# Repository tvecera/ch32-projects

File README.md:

# CH32 Projects

A collection of example projects and experiments for CH32-series microcontrollers from WCH (Nanjing Qinheng
Microelectronics). This repository serves as a personal playground for embedded development with CH32 devices, focusing
on low-cost, open-source hardware hacking.

## Featured Projects

### picopad-ch32prog

- **Description**: RISC-V microcontroller programmer for WCH CH32V, CH32V00X, and CH32V03X series, running on the
  Picopad handheld device. It enables programming CH32 microcontrollers directly from the Picopad's SD card without
  requiring a PC connection.
- **Repository**: [tvecera/ch32-projects/tree/main/picopad-ch32prog](https://github.com/tvecera/ch32-projects/tree/main/picopad-ch32prog)

### ch32-lamp – Music Player (BeatleBeat)

- **Description**: Music module for playing mono WAV (IMA ADPCM) files from an SD card. Based on the BeatleBeat design
  from CH32LibSDK, using the CH32V002x4 MCU. Features BTL PWM output for louder sound without external amplifier.
- **Repository**: [tvecera/ch32-projects/tree/main/ch32-lamp](https://github.com/tvecera/ch32-projects/tree/main/ch32-lamp)

### Tinyboy Console

- **Description**: An adaptation of the CH32V003-GameConsole project by Stefan Wagner for CH32LibSDK, using the
  newer CH32V002J4M6 MCU instead of the discontinued CH32V003. Supports two video outputs: original I2C OLED display
  or RCA composite video output using the rca-library.
- **Repository**: [tvecera/ch32-projects/tree/main/tinyboy](https://github.com/tvecera/ch32-projects/tree/main/tinyboy)

### Olimex RVPC Port to CH32LibSDK

- **Description**: Port of the RVPC (the EURO 1.00 RISC-V personal computer with VGA, keyboard, and Woz-like monitor)
  from Olimex to the CH32LibSDK. In addition to the SDK port, RCA composite video output support has been added
  using the rca-library.
- **Repository**: [tvecera/ch32-projects/tree/main/rvpc](https://github.com/tvecera/ch32-projects/tree/main/rvpc)

### RCA Composite Video Library

- **Description**: A library for generating composite video signal (RCA output) on CH32V002/CH32V003 microcontrollers.
  Supports multiple graphics modes (128x64, 160x120) and text modes (40x30, 32x24, 23x18 characters) with minimal
  RAM and Flash usage. Features both bit-bang and SPI output modes, works with internal oscillator (HSI) or external
  crystal (HSE).
- **Repository**: [tvecera/ch32-projects/tree/main/rca-library](https://github.com/tvecera/ch32-projects/tree/main/rca-library)

### RCA Tester

- **Description**: A simple composite video tester and demonstration of the rca-library capabilities. Generates
  PAL composite video signals with multiple test patterns (grid, crosshatch, circles, checkerboard, etc.) and text
  modes with various fonts. Includes complete hardware design files for DIY manufacturing (KiCAD schematics, PCB
  for laser etching, 3D printable case). Supports both CH32LibSDK and ch32fun frameworks.
- **Repository**: [tvecera/ch32-projects/tree/main/rca-tester](https://github.com/tvecera/ch32-projects/tree/main/rca-tester)

### Pimitachi – 3D Case and Labels

- **Description**: 3D printable case, labels, and laser-etched PCB design for Pimitachi – a Tamagotchi-style virtual pet
  game running on the CH32V002J4M6 MCU. Includes LightBurn project for PCB fabrication with a 10W laser engraver,
  printable labels (photo paper + transparent film), and assembly instructions.
- **Original project**: [Pimitachi on breatharian.eu](https://www.breatharian.eu/hw/ch32libsdk/#pimitachi)
- **Repository**: [tvecera/ch32-projects/tree/main/pimitachi](https://github.com/tvecera/ch32-projects/tree/main/pimitachi)

## Supported Platforms

Build system supports **Linux** and **macOS** (both x86_64 and ARM64/Apple Silicon).

## Getting Started

### Cloning the Repository

This repository uses Git submodules for SDK dependencies. Clone with:

```bash
git clone --recursive https://github.com/tvecera/ch32-projects.git
```

Or if you already cloned without `--recursive`:

```bash
git submodule update --init --recursive
```

### SDK Submodules

The repository includes three SDK submodules in the `sdk/` directory:

| SDK | Description |
|-----|-------------|
| [CH32LibSDK](https://github.com/Panda381/CH32LibSDK) | SDK for CH32V/X series MCUs |
| [PicoLibSDK](https://github.com/Panda381/PicoLibSDK) | SDK for Raspberry Pi Pico / RP2040 / RP2350 |
| [ch32fun](https://github.com/cnlohr/ch32fun) | Lightweight SDK for CH32V003 |

### Required Toolchains

Different projects require different toolchains:

#### For CH32 Projects (ch32-lamp, rvpc, rca-library, tinyboy)

- **RISC-V GCC Toolchain** - `riscv-none-elf-gcc`

**Recommended: xPack RISC-V GCC (cross-platform):**

Download pre-built binaries from [xPack RISC-V GCC releases](https://github.com/xpack-dev-tools/riscv-none-elf-gcc-xpack/releases) and add to PATH.

**macOS/Linux (npm):**
```bash
npm install --location=global @xpack-dev-tools/riscv-none-elf-gcc@latest
```

#### For Picopad Projects (picopad-ch32prog)

- **ARM GCC Toolchain** - `arm-none-eabi-gcc`

**macOS (Homebrew):**
```bash
brew install arm-none-eabi-gcc
```

**Linux (Ubuntu/Debian):**
```bash
sudo apt install gcc-arm-none-eabi
```

#### Additional Tools

- **make** - Build automation
- **minichlink** - CH32 programmer/debugger (included in `tools/minichlink/`)

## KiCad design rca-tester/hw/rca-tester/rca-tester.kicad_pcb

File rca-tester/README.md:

# RCA Tester

A while ago, I purchased a replica of the Sony Walkman CRT screen, which can be found on Chinese
e-shops for a few hundred CZK. The problem is that these screens only support composite video input.
I didn't have any device at home capable of generating a composite video signal. That's why I decided
to create a simple and inexpensive RCA tester.

The RCA Tester serves as both a practical tool for testing composite video displays and a demonstration
of the `rca-library` capabilities. It generates standard PAL composite video signals using just
a cheap RISC-V microcontroller and a few passive components.

**Version 1**

## Features

- **Composite video output** via SPI (hardware) or bit-banging (software)
- **Multiple video modes**: Graphics (pixel-based) and Text (character-based)
- **Test patterns**: 6 pre-built patterns + 2 dynamic patterns
- **Multiple fonts**: Bold, Thin, ZX Spectrum, RVPC, 80-column styles
- **Button input**: 3 buttons with debouncing and auto-repeat
- **Sound synthesis**: PWM audio with melody playback
- **Dual framework support**: Works with both CH32LibSDK and ch32fun

## Supported Microcontrollers

| MCU      | Flash | SRAM | Notes          |
|----------|-------|------|----------------|
| CH32V002 | 16 KB | 4 KB | Default target |
| CH32V003 | 16 KB | 2 KB | Alternative    |

## Video Modes

### Graphics Modes (Pixel-based framebuffer)

| Mode    | Resolution | RAM Usage | Description                 |
|---------|------------|-----------|-----------------------------|
| VMODE 0 | 128x64 px  | ~1.3 KB   | Low resolution, minimal RAM |
| VMODE 1 | 160x120 px | ~2.7 KB   | Higher resolution           |

> **Note:** VMODE 1 requires ~2.7 KB RAM and is only available on CH32V002 (4 KB SRAM).
> CH32V003 with 2 KB SRAM does not have enough memory for this mode.

### Text Modes (Character-based with fonts)

| Mode    | Dimensions  | Font Size | RAM Usage | Description       |
|---------|-------------|-----------|-----------|-------------------|
| VMODE 6 | 40x30 chars | 8x8       | ~1.6 KB   | High density text |
| VMODE 7 | 32x24 chars | 8x8       | ~1.2 KB   | Standard text     |
| VMODE 8 | 23x18 chars | 8x14      | ~0.9 KB   | Large font text   |

## Hardware

**Version 2** (+ PC7 for LED)

### Pin Configuration

| Pin         | Function        | Description                       |
|-------------|-----------------|-----------------------------------|
| **PC6**     | Video Out (SPI) | SPI1_MOSI - hardware video output |
| **PD6**     | Video Out (Alt) | Bit-banging alternative           |
| **PC1**     | Button LEFT/C   | Active-low, internal pull-up      |
| **PC2**     | Button UP/B     | Active-low, internal pull-up      |
| **PC3**     | Button RIGHT/A  | Active-low, internal pull-up      |
| **PC4**     | Audio Out       | PWM on TIM1_CH4                   |
| **PC7**     | LED             | Optional status LED               |
| **PA1/PA2** | Crystal         | External 25 MHz oscillator        |

### Clock Configuration

- **External crystal**: 25 MHz
- **PLL multiplier**: x2
- **System clock**: 50 MHz

### Hardware Design Files

The project is designed for home manufacturing. The `hw/` directory includes everything needed to build the complete
device: a PCB design for a 10W laser, a 3D printable case, and label templates. No professional PCB manufacturing or
specialized equipment (beyond a basic laser engraver and 3D printer) is required.

The `hw/` directory contains all hardware design files:

```
hw/
├── rca-tester/                  # KiCAD 9 project (schematic + PCB) - Version 2
├── rca-tester-case.3mf          # 3D printed case model
├── rca-tester-pcb.lbrn2         # LightBurn project for laser PCB etching - Version 1
├── rca-tester-pcb.png           # PCB image for manual manufacturing - Version 1
├── rca-tester-label.afdesign    # Label template (Affinity Designer)
├── rca-tester-label.docx        # Label template (Word)
└── rca-tester-digram.png        # Block diagram
```

> **Note:** The KiCAD project reflects **Version 2** of the PCB design, which includes these improvements:
> - PC7 pin exposed for optional LED connection
> - Larger crystal socket
>
> The LightBurn/PNG files contain **Version 1** (original design without these features).

#### Manual PCB Manufacturing

The `rca-tester-pcb.lbrn2` and `rca-tester-pcb.png` files are designed for DIY PCB manufacturing using a laser
engraver (10W diode laser recommended).

**Version 1**

### Bill of Materials (BOM)

| Ref     | Component       | Value/Part   | Qty | Notes                                                                                 |
|---------|-----------------|--------------|-----|---------------------------------------------------------------------------------------|
| IC1     | Microcontroller | CH32V002A4M6 | 1   | [AliExpress](https://www.aliexpress.com/item/1005008493381343.html)                   |
| Q1      | Crystal         | 25 MHz       | 1   | HC-49U/S package                                                                      |
| C1      | Capacitor       | 100 nF       | 1   | Ceramic, 1206                                                                         |
| C2, C3  | Capacitor       | 22 pF        | 2   | Ceramic, 1206                                                                         |
| R1      | Resistor        | 470 Ω        | 1   | 1206                                                                                  |
| R2      | Resistor        | 330 Ω        | 1   | 1206                                                                                  |
| R3, R4  | Resistor        | 680 Ω        | 2   | 1206                                                                                  |
| SW1-SW3 | Push Button     | 6x6 mm       | 3   | Tactile switch                                                                        |
| J1      | Header          | 1x4 pin      | 1   | Pin header                                                                            |
| J2      | RCA Connector   | RS-162-DD    | 1   | [GME](https://www.gme.cz/v/1499520/rs-162-zluta-rca-zasuvka)                          |
| J3      | Header          | 1x3 pin      | 1   | Pin header                                                                            |
| J4      | USB Connector   | Micro-B      | 1   | [AliExpress](https://www.aliexpress.com/item/1005007360060905.html) (Micro-28)        |
| BZ1     | Buzzer          | 12 mm        | 1   | [GME](https://www.gme.cz/v/1498245/al-goodwell-al12085mt-p15r-magnetodynamicky-menic) |

Most components are commonly available. The less standard parts with purchase links:

- **RCA Connector (RS-162-DD)** - Available at [GME.cz](https://www.gme.cz/v/1499520/rs-162-zluta-rca-zasuvka)
- **CH32V002A4M6** - RISC-V MCU from WCH, available
  on [AliExpress](https://www.aliexpress.com/item/1005008493381343.html)
- **Micro USB (Micro-28)** - SMD connector, available
  on [AliExpress](https://www.aliexpress.com/item/1005007360060905.html)
- **Buzzer (12 mm)** - Magnetic transducer, available
  at [GME.cz](https://www.gme.cz/v/1498245/al-goodwell-al12085mt-p15r-magnetodynamicky-menic)

## Build System

### Prerequisites

1. **Toolchain**: xpack-riscv-none-elf-gcc (recommended)
    - Download from: https://github.com/xpack-dev-tools/riscv-none-elf-gcc-xpack
    - Note: WCH toolchain has `-flto` bugs, avoid it

2. **Framework** (one of):
    - **CH32LibSDK**: https://github.com/Panda381/CH32LibSDK
    - **ch32fun**: https://github.com/cnlohr/ch32fun

3. **Environment setup**:
   ```bash
   export PATH="/path/to/xpack-riscv-none-elf-gcc/bin:$PATH"
   export CH32_ROOT_PATH="/path/to/CH32LibSDK"
   ```

### Build Scripts

All scripts accept optional parameters: `[sdk] [mcu]`

| Script | Function              | Example                      |
|--------|-----------------------|------------------------------|
| `c.sh` | Build/Compile         | `./c.sh ch32libsdk ch32v003` |
| `d.sh` | Clean                 | `./d.sh`                     |
| `e.sh` | Flash to device       | `./e.sh ch32fun ch32v002`    |
| `r.sh` | Reset device          | `./r.sh`                     |
| `a.sh` | Clean + Build         | `./a.sh`                     |
| `x.sh` | Clean + Build + Flash | `./x.sh`                     |

**Default values**: `sdk=ch32libsdk`, `mcu=ch32v002`

### Quick Start

```bash
# Full rebuild and flash with defaults
./x.sh

# Build for CH32V003 with CH32LibSDK
./x.sh ch32libsdk ch32v003

# Just compile (no flash)
./c.sh

# Clean build artifacts
./d.sh
```

## Configuration

Edit `config.h` to customize the firmware:

### Video Mode Selection

```c
#define VMODE 0     // 0=128x64, 1=160x120, 6=40x30 text, 7=32x24 text, 8=23x18 text
```

### Video Output Method

```c
#define USE_RCA_SPI 1   // 1=SPI hardware (PC6), 0=bit-bang (PD6)
```

### Clock Source

```c
#define USE_HSI 0       // 0=external 25MHz crystal, 1=internal oscillator
```

### Feature Enables

```c
#define USE_KEYS  1     // Enable button input
#define USE_SOUND 2     // 0=disabled, 1=tones only, 2=melody playback
```

## Usage

### Graphics Mode (VMODE 0/1)

The application cycles through 8 test patterns:

1. **Grid** - Regular grid lines
2. **Crosshatch** - Diagonal crossing lines
3. **Circles** - Concentric circles
4. **Border** - Screen border frame
5. **Checkerboard** - Alternating squares
6. **Dots** - Dot matrix pattern
7. **Text** - "RCA Video" text display
8. **Charset** - Full character set display

**Controls**:

- **RIGHT (A)** - Next pattern
- **LEFT (C)** - Previous pattern
- **UP (B)** - Reset to bootloader

### Text Mode (VMODE 6/7/8)

The application showcases different fonts:

- TextModeFontBold8x8
- TextModeFontThin8x8
- TextModeFontZx
- TextModeFontRvpc
- TextModeFont80
- TextModeFont81

## Pattern Conversion

The conversion scripts generate C header files containing the pattern data, which are then included in the project.

### Convert PNG to C array

```bash
cd patterns

# For VMODE 0 (128x64)
python3 convert.py vmode0/01_pattern_grid.png > pattern_grid.h

# For VMODE 1 with RLE compression (160x120)
python3 convert_rle.py vmode1/01_pattern_grid.png > pattern_grid_rle.h
```

### Requirements

- Python 3
- Pillow library: `pip3 install pillow`

## Dependencies

### rca-library

The shared video generation library located at `../rca-library/`:

- Video signal timing and generation
- Multiple font files (8x8, 8x14, various styles)
- SPI and bit-bang rendering modes
- Frame callback mechanism

### Frameworks

Both frameworks are included in the repository as git submodules in `../sdk/`:

```bash
# Initialize submodules after cloning
git submodule update --init --recursive
```

**CH32LibSDK** by Miroslav Nemecek (Panda38):

- https://github.com/Panda381/CH32LibSDK
- Location: `../sdk/CH32LibSDK/`
- Full peripheral drivers
- Comprehensive hardware abstraction

**ch32fun** by CNLohr:

- https://github.com/cnlohr/ch32fun
- Location: `../sdk/ch32fun/`
- Lightweight alternative
- Minimal overhead

## License

MIT License - See source file headers for details.

Portions derived from CH32LibSDK by Miroslav Nemecek (Panda38) retain their original license.

## Links

- [CH32LibSDK](https://github.com/Panda381/CH32LibSDK)
- [ch32fun](https://github.com/cnlohr/ch32fun)
- [RISC-V Toolchain](https://github.com/xpack-dev-tools/riscv-none-elf-gcc-xpack)

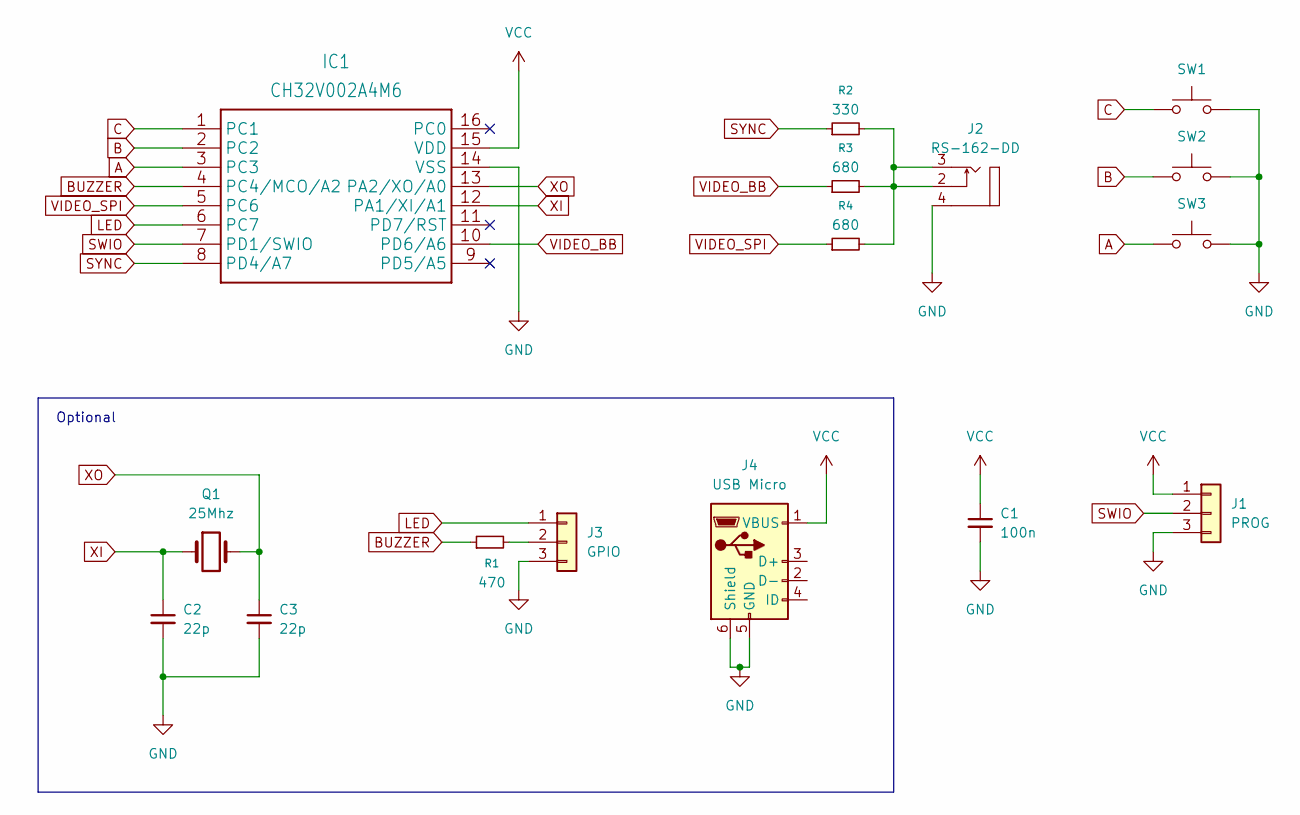
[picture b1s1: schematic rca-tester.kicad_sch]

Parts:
C1: 100n; C_1206_3216Metric_Pad1.33x1.80mm_HandSolder
C2, C3: 22p; C_1206_3216Metric_Pad1.33x1.80mm_HandSolder
IC1: CH32V002A4M6; SOP-16_4.55x10.3mm_P1.27mm
J1: PROG; PinSocket_1x03_P2.54mm_Vertical
J2: RS-162-DD
J3: GPIO; PinSocket_1x05_P2.54mm_Vertical
J4: USB Micro; USB_Micro-B_Amphenol_10118194_Horizontal
Q1: 25Mhz; PinSocket_1x03_P2.54mm_Vertical
R1: 470; R_1206_3216Metric_Pad1.30x1.75mm_HandSolder
R2: 330; R_1206_3216Metric_Pad1.30x1.75mm_HandSolder
R3, R4: 680; R_1206_3216Metric_Pad1.30x1.75mm_HandSolder
SW1, SW2, SW3: SW_Push; SW_PUSH_6mm

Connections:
A: IC1.3 (PC3), SW3.1
B: IC1.2 (PC2), SW2.1
BUZZER: IC1.4 (PC4/MCO/A2), R1.1
C: IC1.1 (PC1), SW1.1
GND: C1.2, C2.2, C3.2, IC1.14 (VSS), J1.3, J2.4, J3.3, J4.5 (GND), J4.6 (Shield), SW1.2, SW2.2, SW3.2
LED: IC1.6 (PC7), J3.1
unnamed: J2.2, J2.3, R2.2, R3.2, R4.2
unnamed: J3.2, R1.2
SWIO: IC1.7 (PD1/SWIO), J1.2
SYNC: IC1.8 (PD4/A7), R2.1
VCC: C1.1, IC1.15 (VDD), J1.1, J4.1 (VBUS)
VIDEO_BB: IC1.10 (PD6/A6), R3.1
VIDEO_SPI: IC1.5 (PC6), R4.1
XI: C2.1, IC1.12 (PA1/XI/A1), Q1.1
XO: C3.1, IC1.13 (PA2/XO/A0), Q1.2

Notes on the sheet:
Optional

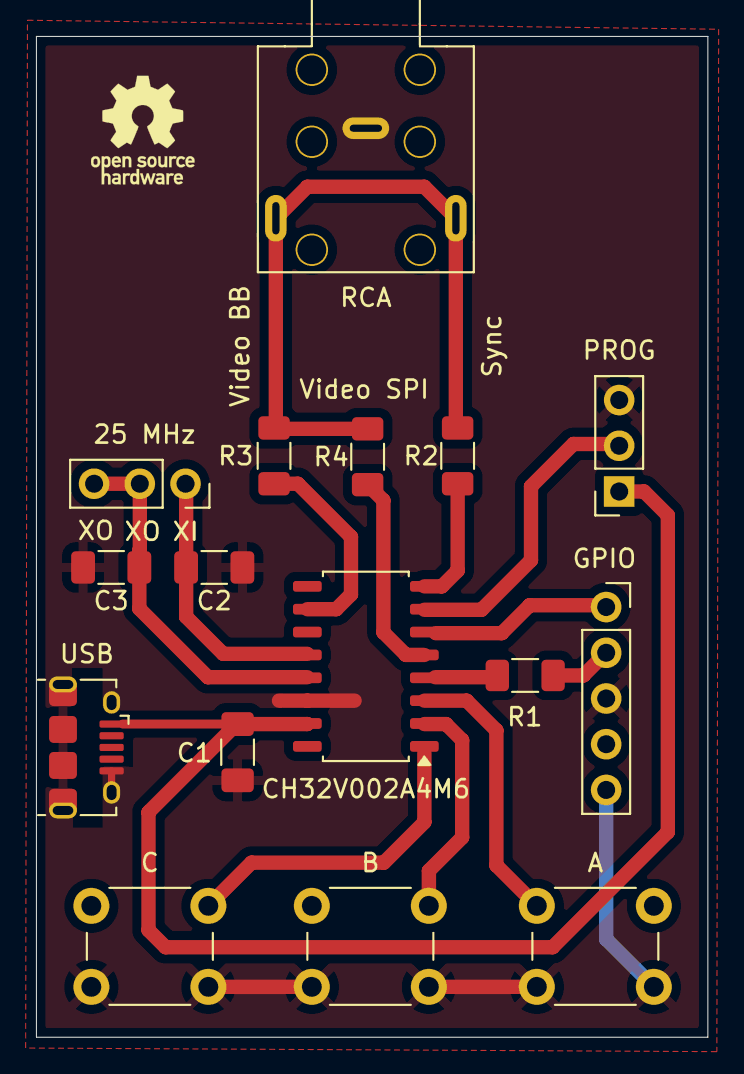
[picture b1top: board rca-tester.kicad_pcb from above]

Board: 2 copper layers, 37.3 x 55.6 mm, 16 parts (0 on the bottom side), 15 nets.

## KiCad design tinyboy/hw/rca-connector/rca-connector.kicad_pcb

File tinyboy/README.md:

bu# Tinyboy

**Tinyboy console** is based on the [CH32V003-GameConsole](https://github.com/wagiminator/CH32V003-GameConsole) project
by Stefan Wagner.  
Instead of the now discontinued CH32V003, it uses the newer **CH32V002J4M6** MCU.  
I used version 1.1 of the PCB design, which does not include the transistor for the buzzer.

**CH32V003-GameConsole PCB v1.1**

- https://oshwlab.com/wagiminator/ch32v003j4m6-game-console
- https://github.com/wagiminator/CH32V003-GameConsole/tree/main/hardware

---

## Schematic

The Tinyboy console does **not include the 6th button (KEY_B)**. Fortunately, most games in **CH32LibSDK** do not
require this button.

---

## Video Output

TinyBoy supports two video output options:

### OLED Display (I2C)

The default video output uses a **0.96" I2C OLED display** (128×64 pixels, SSD1306 controller).
This is the standard configuration inherited from the original CH32V003-GameConsole design.

### RCA Composite Video

As an alternative, you can output video to a **TV or monitor** via composite video (RCA connector).
This mode uses the [rca-library](../rca-library/) from this repository.

The I2C pins are repurposed with a simple resistor DAC:

| Pin | Resistor | Signal |
|-----|----------|--------|
| SDA | 330Ω     | SYNC   |
| SCL | 680Ω     | VIDEO  |
| GND | —        | GND    |

Connect SYNC + VIDEO to the **center pin** of the RCA connector, and GND to the **outer ring**.

#### RCA Connector Adapter

A simple adapter PCB is available in [hw/rca-connector](hw/rca-connector/) (KiCad project).

**Schematic:**

**PCB for manual fabrication:**

**Additional files:**

- [rca-connector-label.pdf](hw/rca-connector-label.pdf) – printable labels
- [rca-connector.lbrn2](hw/rca-connector.lbrn2) – LightBurn project file (for 10W laser engraver)

#### Build Configuration

Each game directory contains shell scripts for building and flashing:

| Script | Description                        |
|--------|------------------------------------|
| `c.sh` | Compile (incremental build)        |
| `a.sh` | All – clean + compile              |
| `d.sh` | Delete – clean build artifacts     |
| `e.sh` | Export – flash to hardware + reset |
| `r.sh` | Reset device                       |
| `x.sh` | Full rebuild + flash (a.sh + e.sh) |

The video output is selected by passing `0` (OLED) or `1` (RCA) as argument:

```bash
# Build for OLED display (default)
./c.sh 0

# Build for RCA composite video output
./c.sh 1

# Full clean rebuild + flash for RCA
./x.sh 1
```

For RCA mode, you can also select the video resolution using `VMODE` environment variable:

| VMODE | Resolution | Framebuffer |
|-------|------------|-------------|
| 0     | 128×64     | 1024 B      |
| 1     | 160×120    | 2400 B      |

```bash
# Build for RCA with higher resolution
VMODE=1 ./c.sh 1
```

**Note:** RCA mode uses a different clock configuration (50 MHz via PLL instead of 24 MHz HSI) to achieve accurate video
timing.

---

## Programming

Programming the console is straightforward using the **WCH-LinkE programmer**.  
Simply connect:

- **SWDIO** from programmer → **DIO**
- **3V3**
- **GND**

The standard tool is **WCH-LinkUtility**, but it is **only available for Windows**.  
For Linux and macOS, alternatives are needed:

### [rvprog](https://github.com/wagiminator/MCU-Flash-Tools?tab=readme-ov-file#rvprog)

- Easy installation (`pip install rvprog`)
- Limitation: fails to upload larger programs (>10 KB) completely into MCU flash

### [minichlink](https://github.com/cnlohr/ch32fun/tree/master/minichlink)

- The **most reliable tool** in my experience
- Can reset the MCU even without the reset pin connected
- Automatically detects the WCH-LinkE programmer
- Supports alternative programmers (e.g., via **esp32s2chfun**)
- Drawback: must be compiled manually
    - On macOS I had to remove support for `b003boot` and `esp32s2chfun` to build successfully

Prebuilt binaries for **macOS** and **Linux** are available in the `../tools` folder.

---

## Battery Measurement

A nice advantage of the Tinyboy console is that it has **no voltage regulator** – the MCU is powered directly from the
battery. This allows you to **measure the battery voltage** using the internal **1.2 V reference** of the CH32V002.

### Example Usage

```c
// The value bat will return the battery voltage in millivolts (mV).

BatInit();
const u32 bat = GetBat();
BatTerm();
```

**Notes**

- The function uses ADC1 in single conversion mode.
- The computation scales the internal 1.2 V reference to the actual supply voltage.
- If you use the KEY service, it must be temporarily disabled while reading the ADC.
- Returns the voltage in millivolts (mV).

---

## Expansion Possibilities

Because the MCU is in an **SOP-8 package**, the number of available pins is very limited.  
Still, some expansions are possible:

- The **OLED pins** can also be used to connect an **I2C sensor**.  
  With software I2C, you can easily turn the console into a **simple sensor device**.

- Another option is to reuse the **SWIO programming pin**.  
  The SDK provides functions to remap it:

```c
// PD1 as standard GPIO
GPIO_Remap_SWD(4);

// Restore PD1 as SWIO (programming)
GPIO_Remap_SWD(0);
```

⚠️ **Warning:** After remapping PD1 to GPIO, programming will no longer work.  
The only recovery option is a **power cycle erase** ("unbrick chip").  
It is therefore wise to add a small delay at the start of `main()` to allow erasing via programmer,  
or only remap this pin after pressing a button.

---

## Assembly

Assembly is relatively simple, but some parts (battery holder, on/off switch, buzzer) may be harder to source.  
**Tip:** Solder the OLED display **last** – otherwise it becomes tricky to mount the on/off switch properly.

With PCB ordered from JLCPCB, the total cost is around **100–200 CZK** (≈ 4–8 EUR).

---

## Parts List

| Component                        | Link                                                                                                                                                                                                                                                 | Price    |
|----------------------------------|------------------------------------------------------------------------------------------------------------------------------------------------------------------------------------------------------------------------------------------------------|----------|
| **MCU CH32V002J4M6**             | [AliExpress](https://www.aliexpress.com/item/1005009035485168.html)                                                                                                                                                                                  | ~2 Kč    |
| **Buzzer – MLT-5030**            | [AliExpress](https://www.aliexpress.com/item/1005008979086407.html)                                                                                                                                                                                  | ~8 Kč    |
| **Battery Holder (CR2032)**      | [AliExpress](https://www.aliexpress.com/item/1005005960185390.html), [TME](https://www.tme.eu/cz/details/ch28-2032/baterie-pouzdra-i-drzaky/comf/ch28-2032lf/)                                                                                       | 6–25 Kč  |
| **Rechargeable Battery LIR2032** | [Laskakit](https://www.laskakit.cz/lir2032-li-ion-baterie-40mah-3-6v/), [AliExpress](https://www.aliexpress.com/item/1005008971074671.html)                                                                                                          | 16–58 Kč |
| **I2C OLED 0.96" (128x64)**      | [Pajenicko](https://pajenicko.cz/graficky-oled-displej-096-128x64-i2c-bily), [AliExpress](https://www.aliexpress.com/item/1005006141235306.html)                                                                                                     | 40–89 Kč |
| **ON/OFF Switch**                | [Laskakit](https://www.laskakit.cz/alps-ssss811101-posuvny-prepinac-5vdc-300ma--smd/), [TME](https://www.tme.eu/cz/details/cus-12tb/posuvne-prepinace/nidec-copal-electronics/), [AliExpress](https://www.aliexpress.com/item/1005006710234187.html) | 3–22 Kč  |
| **Tactile Buttons (6×6 mm)**     | [Pajenicko](https://pajenicko.cz/mikrospinac-6x6x5mm-1ts005f), [Laskakit](https://www.laskakit.cz/tlacitko-6x6x5mm/), [Laskakit SMD](https://www.laskakit.cz/tlacitko-smd-6x6x8mm/)                                                                  | ~2 Kč    |
| **RS-162 - RCA connector**       | [GME](https://www.gme.cz/v/1499520/rs-162-zluta-rca-zasuvka)                                                                                                                                                                                         | ~11 Kč   |

---

## Notes & Recommendations

- Games from **CH32LibSDK** run smoothly despite the missing **KEY_B button**.
- For portable use, a **rechargeable LIR2032** is recommended instead of a standard CR2032, as some games and the OLED
  can quickly drain a regular battery.
- The design is compact and inexpensive, making it a great **DIY retro handheld project**.

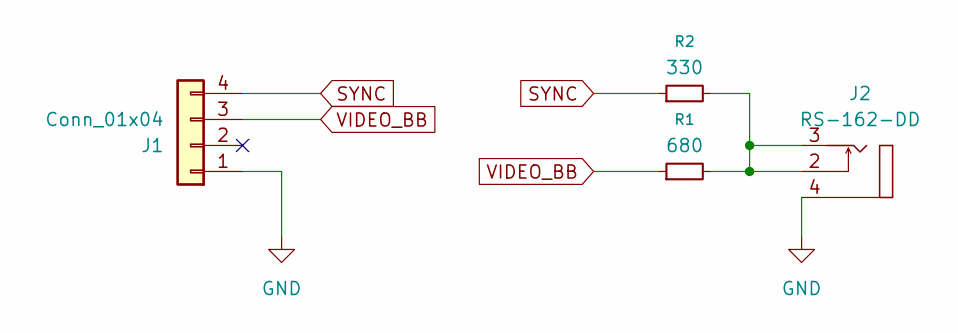
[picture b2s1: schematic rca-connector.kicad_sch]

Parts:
J1: Conn_01x04; PinHeader_1x04_P2.54mm_Vertical
J2: RS-162-DD
R1: 680; R_1206_3216Metric_Pad1.30x1.75mm_HandSolder
R2: 330; R_1206_3216Metric_Pad1.30x1.75mm_HandSolder

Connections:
GND: J1.1, J2.4
unnamed: J2.2, J2.3, R1.2, R2.2
SYNC: J1.4, R2.1
VIDEO_BB: J1.3, R1.1

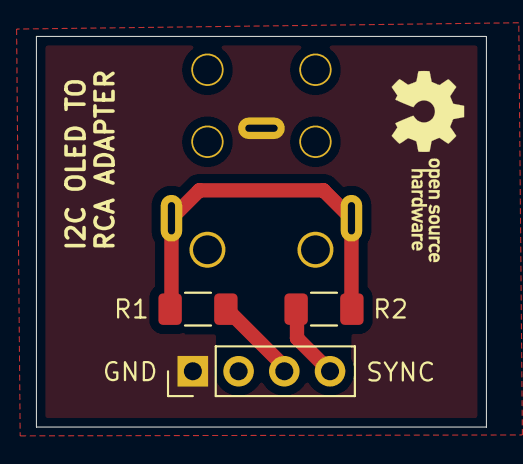
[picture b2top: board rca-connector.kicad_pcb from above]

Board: 2 copper layers, 25.0 x 21.7 mm, 4 parts (1 on the bottom side), 4 nets.

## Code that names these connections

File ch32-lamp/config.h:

// ****************************************************************************
//                                 
//                        Project library configuration
//
// ****************************************************************************

#ifndef _CONFIG_H
#define _CONFIG_H

#define BEATLEBEAT	1	// 1 = use BeatleBeat device

#if BABYBEAT		// 1 = use BabyBeat device
#define SYSTICK_KEYSCAN	1	// 1=call KeyScan() function from SysTick system timer
#else
#define SYSTICK_KEYSCAN	0	// 1=call KeyScan() function from SysTick system timer
#endif

// ----------------------------------------------------------------------------
//                            Clock Setup
// ----------------------------------------------------------------------------

// frequency of HSI internal oscillator 48MHz
#define HSI_VALUE	24000000

// System clock source: 1=HSI, 2=HSE, 3=HSE_Bypass, 4=PLL_HSI, 5=PLL_HSE, 6=PLL_HSE_Bypass, 7=PLL_HSI/2, 8=PLL_HSE/2, 9=PLL_HSE_Bypass/2
#define SYSCLK_SRC	4

// PLL multiplier
#define PLLCLK_MUL	2		// only *2 supported; 24 MHz * 2 = 48 MHz

// System clock divider: 1, 2, 3, 4, 5, 6, 7, 8, 16, 32, 64, 128, 256 (default 1)
#define SYSCLK_DIV	1

// ADC clock divider: (1,) 2, 4, 6, 8, 12, 16, 24, 32, 48, 64, 96, 128 (default 1 or 2)
#define ADCCLK_DIV	8		// CH32V0: max. 24 MHz (48 / 8 = 6 MHz)

// number of HCLK clock cycles per 1 us (used with Wait functions)
// - If you want to change frequency of system clock run-time, use a variable instead of constant.
#define HCLK_PER_US	48

// increment of system time in [ms] on SysTick interrupt (0=do not use SysTick interrupt)
#if BABYBEAT		// 1 = use BabyBeat device
#define SYSTICK_MS	20
#else
#define SYSTICK_MS	0
#endif

// ----------------------------------------------------------------------------
//                          Peripheral clock enable
// ----------------------------------------------------------------------------

#define ENABLE_SRAM	1		// SRAM enable
#define ENABLE_FLASH	0		// FLASH enable
#define ENABLE_WWDG	0		// Window watchdog enable
#define ENABLE_PWR	1		// Power module enable
#define ENABLE_AFI	1		// I/O auxiliary function enable
#define ENABLE_PA	1		// PA port enable
#define ENABLE_PB	0		// PB port enable
#define ENABLE_PC	1		// PC port enable
#define ENABLE_PD	1		// PD port enable
#define ENABLE_ADC1	0		// ADC1 module enable
#define ENABLE_TIM1	1		// TIM1 module enable
#define ENABLE_TIM2	0		// TIM2 module enable
#define ENABLE_TIM3	0		// TIM3 module enable
#define ENABLE_SPI1	0		// SPI1 module enable
#define ENABLE_USART1	0		// USART1 module enable
#define ENABLE_I2C1	0		// I2C1 module enable
#define ENABLE_DMA1	0		// DMA1 module enable

// ----------------------------------------------------------------------------
//                            Library modules
// ----------------------------------------------------------------------------

#define USE_CRC		0	// 1=use CRC library
#define USE_DECNUM	0	// 1=use decode number
#define USE_FAT		1	// 1=use FAT filesystem
#define USE_RAND	0	// 1=use random number generator

// SD card
#if BABYBEAT		// 1 = use BabyBeat device
#define USE_SD		4	// use SD card driver: 0=no, 1=software, 2=hardware, 3=software with fast read, 4=hardware with software CS
#define SD_CS_GPIO	PA1	// CS output to SD card
#define SD_CLK_GPIO	PD4	// CLK output to SD card
#define SD_MISO_GPIO	PD5	// MISO input from SD card
#define SD_MOSI_GPIO	PD6	// MOSI output to SD card
#define SD_SPEED_INIT	(HCLK_PER_US*2)	// SD speed on init: wait delay "HCLK_PER_US*2" = 250 kbps
#define SD_SPEED_READ	3	// (working value 0..3) SD speed on read: wait delay "HCLK_PER_US/8" = 4 Mbps
#define SD_SPEED_WRITE	(HCLK_PER_US/2)	// SD speed on write: wait delay "HCLK_PER_US/2" = 1 Mbps
//	4 ... PD3:CS, PD4:SCK, PD5:MISO, PD6:MOSI
#define SD_SPI_MAP	4	// hardware SD card driver: SPI mapping
#define SD_SPI_DIV_INIT	7	// hardware SD card driver: SPI baud divider 0..7 (means div=2..256) on init
#define SD_SPI_DIV_READ	2	// (working value 0..6) hardware SD card driver: SPI baud divider 0..7 (means div=2..256) on read
#define SD_SPI_DIV_WRITE 6	// hardware SD card driver: SPI baud divider 0..7 (means div=2..256) on write
#else // BABYBEAT
// SD card
#define USE_SD		3	// use SD card driver: 0=no, 1=software, 2=hardware, 3=software with fast read, 4=hardware with software CS
#define SD_CS_GPIO	PC4	// CS output to SD card
#define SD_CLK_GPIO	PC2	// CLK output to SD card
#define SD_MISO_GPIO	PC1	// MISO input from SD card
#define SD_MOSI_GPIO	PD1	// MOSI output to SD card
#define SD_SPEED_INIT	(HCLK_PER_US*2)	// SD speed on init: wait delay "HCLK_PER_US*2" = 250 kbps
#define SD_SPEED_READ	3	// (working value 0..3) SD speed on read: wait delay "HCLK_PER_US/8" = 4 Mbps
#define SD_SPEED_WRITE	(HCLK_PER_US/2)	// SD speed on write: wait delay "HCLK_PER_US/2" = 1 Mbps
#endif // BABYBEAT

// ----------------------------------------------------------------------------
//                             SDK modules
// ----------------------------------------------------------------------------

#define USE_ADC		0	// 1=use ADC peripheral
#define USE_DMA		0	// 1=use DMA peripheral
#define USE_FLASH	0	// 1=use Flash programming
#define USE_I2C		0	// 1=use I2C peripheral
#define USE_IRQ		1	// 1=use IRQ interrupt support
#define USE_PWR		1	// 1=use power control
#define USE_SPI		0	// 1=use SPI peripheral
#define USE_TIM		1	// 1=use timers
#define USE_USART	0	// 1=use USART peripheral

#endif // _CONFIG_H

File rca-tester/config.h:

/**
 * MIT License
 *
 * Copyright (c) 2025 Tomas Vecera, tomas@vecera.dev
 *
 * Permission is hereby granted, free of charge, to any person obtaining a copy
 * of this software and associated documentation files (the "Software"), to deal
 * in the Software without restriction, including without limitation the rights
 * to use, copy, modify, merge, publish, distribute, sublicense, and/or sell
 * copies of the Software, and to permit persons to whom the Software is
 * furnished to do so, subject to the following conditions:
 *
 * The above copyright notice and this permission notice shall be included in all
 * copies or substantial portions of the Software.
 *
 * THE SOFTWARE IS PROVIDED "AS IS", WITHOUT WARRANTY OF ANY KIND, EXPRESS OR
 * IMPLIED, INCLUDING BUT NOT LIMITED TO THE WARRANTIES OF MERCHANTABILITY,
 * FITNESS FOR A PARTICULAR PURPOSE AND NONINFRINGEMENT. IN NO EVENT SHALL THE
 * AUTHORS OR COPYRIGHT HOLDERS BE LIABLE FOR ANY CLAIM, DAMAGES OR OTHER
 * LIABILITY, WHETHER IN AN ACTION OF CONTRACT, TORT OR OTHERWISE, ARISING FROM,
 * OUT OF OR IN CONNECTION WITH THE SOFTWARE OR THE USE OR OTHER DEALINGS IN THE
 * SOFTWARE.
 *
 * ============================================================================
 * RCA Tester Configuration
 * ============================================================================
 *
 * Main configuration file for rca-tester application.
 * Defines video mode, clock source, and feature enables.
 *
 * ============================================================================
 */

#ifndef _CONFIG_H
#define _CONFIG_H

// ============================================================================
// Video Mode Selection
// ============================================================================
// Available video modes (B&W monochrome):
//
// Graphics modes (FrameBuf = pixels):
//   VMODE 0: 128x64 px,  RAM: 1024B buf + 306B handler = 1330B total
//   VMODE 1: 160x120 px, RAM: 2400B buf + 330B handler = 2730B total - Only for CH32V002
//
// Text modes (FrameBuf = ASCII characters, requires font in Flash):
//   VMODE 6: 40x30 chars (8x8 font),  RAM: 1200B buf + 20B state + 376B handler = 1596B
//   VMODE 7: 32x24 chars (8x8 font),  RAM: 768B buf + 20B state + 430B handler = 1218B
//   VMODE 8: 23x18 chars (8x14 font), RAM: 414B buf + 64B state + 418B handler = 896B
//
// Font Flash usage: 64 chars = 2048B, 128 chars = 4096B
#define VMODE           0

// Video output method:
//   USE_RCA_SPI = 0: Bit-banging on PD6 (default, works on all pins)
//   USE_RCA_SPI = 1: SPI1 MOSI on PC6 (hardware shift, frees CPU during pixel output)
//
// SPI mode requires PC6 for video output (SPI1_MOSI default pin)
// Bit-bang mode uses PD6 (can be changed in rca.c)
#define USE_RCA_SPI     1

// Clock source selection:
//   USE_HSI = 1: Internal HSI oscillator (no external crystal needed)
//                Less accurate, may cause slight timing drift
//   USE_HSI = 0: External HSE crystal oscillator (requires 25MHz crystal on PA1/PA2)
//                More accurate and stable timing for video sync
#define USE_HSI         0

// ============================================================================
// Application Features
// ============================================================================
#define USE_KEYS        1
#define USE_SOUND       2

// ============================================================================
// Font Selection
// ============================================================================
#if VMODE == 0 || VMODE == 1
#define FONT            FontBold8x8             // Graphics font (1KB or 2KB) for draw.c
// #else
// #define FONT            TextModeFontRvpc     // Text mode font descriptor (64 or 128 chars)
#endif

// ============================================================================
// Clock Configuration
// ============================================================================
#if USE_HSI
// frequency of HSI internal oscillator 25MHz
#define HSI_VALUE       25000000
// System clock source: 1=HSI, 2=HSE, 3=HSE_Bypass, 4=PLL_HSI, 5=PLL_HSE, 6=PLL_HSE_Bypass
#define SYSCLK_SRC      4

#else
// frequency of HSE external oscillator 25MHz
#define HSE_VALUE       25000000
// frequency of HSI internal oscillator 25MHz
#define HSI_VALUE       25000000
// System clock source: 1=HSI, 2=HSE, 3=HSE_Bypass, 4=PLL_HSI, 5=PLL_HSE, 6=PLL_HSE_Bypass
#define SYSCLK_SRC      5
#endif

// Only *2 supported; 25 MHz * 2 = 50 MHz
#define PLLCLK_MUL      2
// System clock divider: 1, 2, 3, 4, 5, 6, 7, 8, 16, 32, 64, 128, 256 (default 1)
#define SYSCLK_DIV      1

// ADC clock divider: (1,) 2, 4, 6, 8, 12, 16, 24, 32, 48, 64, 96, 128 (default 1 or 2)
#define ADCCLK_DIV      2                       // CH32V0: max. 24 MHz (48 / 2 = 24 MHz)

// number of HCLK clock cycles per 1 us (used with Wait functions)
// - If you want to change frequency of system clock run-time, use a variable instead of constant.
#define HCLK_PER_US     50

// increment of system time in [ms] on SysTick interrupt (0=do not use SysTick interrupt)
#define SYSTICK_MS      0

// ============================================================================
// Peripherals
// ============================================================================
#define ENABLE_SRAM     1                       // SRAM enable
#define ENABLE_FLASH    1                       // FLASH enable (needed to rewrite RESET function)
#define ENABLE_WWDG     0                       // Window watchdog enable
#define ENABLE_PWR      1                       // Power module enable
#define ENABLE_AFI      1                       // I/O auxiliary function enable
#define ENABLE_PA       1                       // PA port enable
#define ENABLE_PB       0                       // PB port enable
#define ENABLE_PC       1                       // PC port enable
#define ENABLE_PD       1                       // PD port enable
#define ENABLE_TIM1     1                       // TIM1 module enable
#define ENABLE_TIM2     1                       // TIM2 module enable
#if USE_RCA_SPI
#define ENABLE_SPI1     1                       // SPI1 module enable (required for SPI video output)
#else
#define ENABLE_SPI1     0                       // SPI1 module enable
#endif
#define ENABLE_USART1   0                       // USART1 module enable
#define ENABLE_I2C1     0                       // I2C1 module enable

#include "../rca-library/rca_config.h"

#endif //_CONFIG_H

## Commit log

2025-10-19 Add RVPC
2025-12-21 Add ch32-lamp - music player for "Christmas lamp"
    Add ch32-lamp - music player for "Christmas lamp"
2025-12-26 Add Pimitachi – 3D Case and Labels
2026-01-04 Add RCA library and new version of the RVPC CH32LIBSDK port.
    rca library
2026-01-10 Add sdk submodules
2026-01-10 Add Tinyboy
2026-01-10 Add RCA support for Tinyboy
2026-01-12 Add RCA tester
2026-01-12 Update README.md, add RCA tester.
